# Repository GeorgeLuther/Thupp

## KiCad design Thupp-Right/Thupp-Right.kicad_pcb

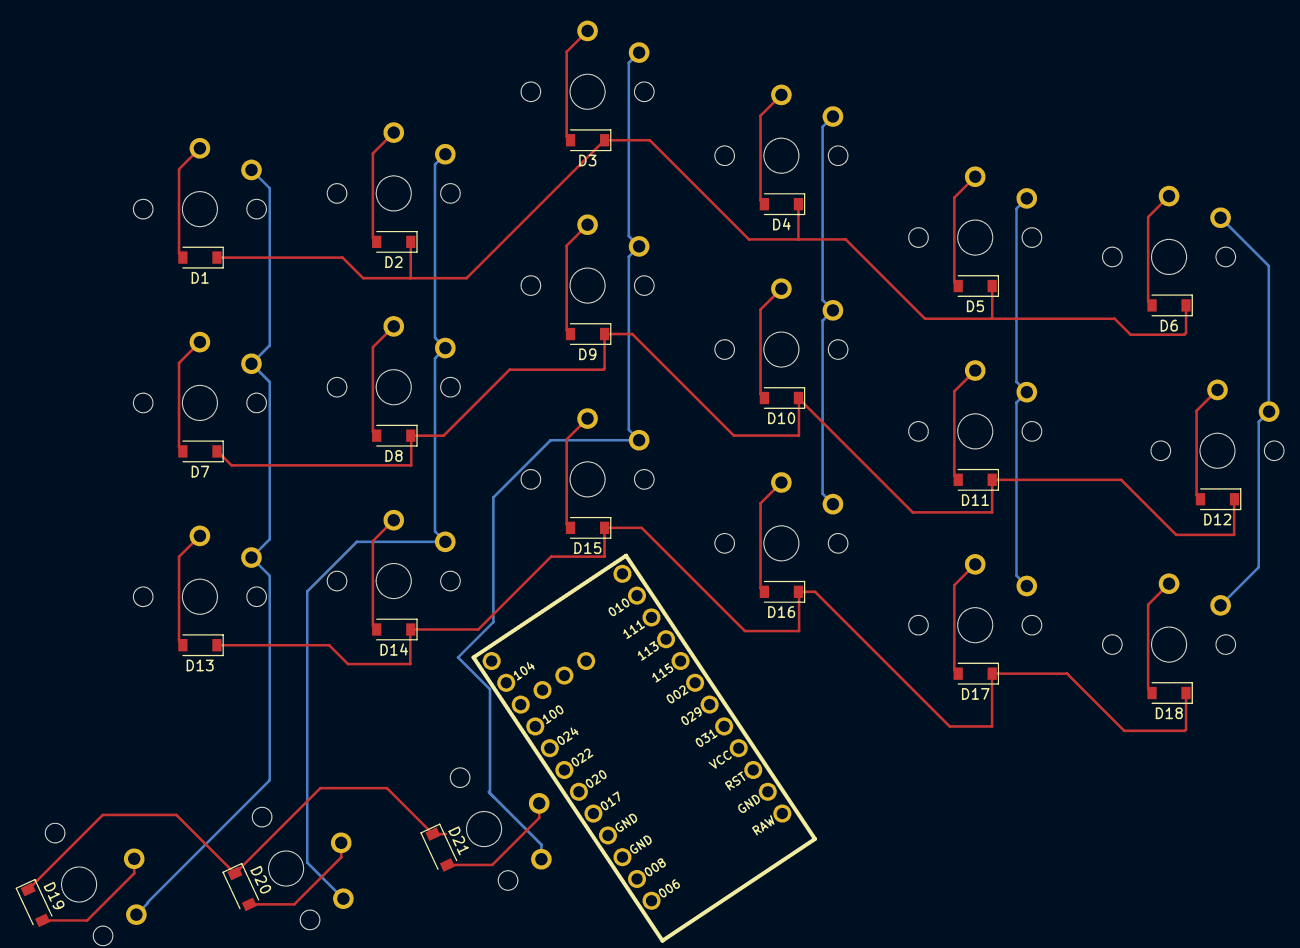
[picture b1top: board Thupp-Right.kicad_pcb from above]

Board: 2 copper layers, 43 parts (1 on the bottom side), 31 nets.

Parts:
D1, D2, D3, D4, D5, D6, D7, D8, D9, D10, D11, D12, D13, D14, D15, D16, D17, D18, D19, D20, D21: D_Small; D_SOD-123
MX1, MX2, MX3, MX4, MX5, MX6, MX7, MX8, MX9, MX10, MX11, MX13, MX14, MX15, MX16, MX17, MX18: MX-NoLED; KailhChoc-1U
MX12, MX20, MX21: MX-NoLED; KailhChoc-1.5U
MX19: MX-NoLED; KailhChoc-2U
U1: nice_nano

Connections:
COL0: MX1.1, MX7.1, MX13.1, MX19.1, U1.1
COL1: MX2.1, MX8.1, MX14.1, MX20.1, U1.2
COL2: MX3.1, MX9.1, MX15.1, MX21.1, U1.5
COL3: MX4.1, MX10.1, MX16.1
COL4: MX5.1, MX11.1, MX17.1
COL5: MX6.1, MX12.1, MX18.1
unnamed: D1.2, MX1.2
unnamed: D2.2, MX2.2
unnamed: D3.2, MX3.2
unnamed: D4.2, MX4.2
unnamed: D5.2, MX5.2
unnamed: D6.2, MX6.2
unnamed: D7.2, MX7.2
unnamed: D8.2, MX8.2
unnamed: D9.2, MX9.2
unnamed: D10.2, MX10.2
unnamed: D11.2, MX11.2
unnamed: D12.2, MX12.2
unnamed: D13.2, MX13.2
unnamed: D14.2, MX14.2
unnamed: D15.2, MX15.2
unnamed: D16.2, MX16.2
unnamed: D17.2, MX17.2
unnamed: D18.2, MX18.2
unnamed: D19.2, MX19.2
unnamed: D20.2, MX20.2
unnamed: D21.2, MX21.2
ROW0: D1.1, D2.1, D3.1, D4.1, D5.1, D6.1
ROW1: D7.1, D8.1, D9.1, D10.1, D11.1, D12.1
ROW2: D13.1, D14.1, D15.1, D16.1, D17.1, D18.1
ROW3: D19.1, D20.1, D21.1, U1.8

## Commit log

2021-10-27 KiCad Right established, first commit
2021-10-27 added submodules
2021-10-27 installed submodules
2021-10-27 Fixed footprint library managment, assigned footprint bindings.
2021-10-29 added crides footprint with diode
2021-10-29 footprints placed
2021-10-30 aligned footprints relative to plate
2021-10-31 adding col assn to nice!nano
2021-11-01 fully routed 1st attempt
